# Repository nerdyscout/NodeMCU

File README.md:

# NodeMCU

collection of various PCBs fitting the NodeMCU_ESP8266

## [PIS](PIS) 
- Plant Irrigation System

## [IR](IR) 
- IR-MQTT-Bridge

## [PWR](PWR) 
230V AC phase dimmer

## [CO2](CO2) 
CO2 Measurment with ESP8266
- data can be send via LoRa

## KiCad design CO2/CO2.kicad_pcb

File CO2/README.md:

# NodeMCU_CO2

Shield for the NodeMCU_ESP8266 for builing a CO2 measurment device.

## Schematic

## Layout

## Documentation 
- Assemble all parts according [BOM](gerbers/CO2_BOM_CO2.csv)

#### Software
tbd

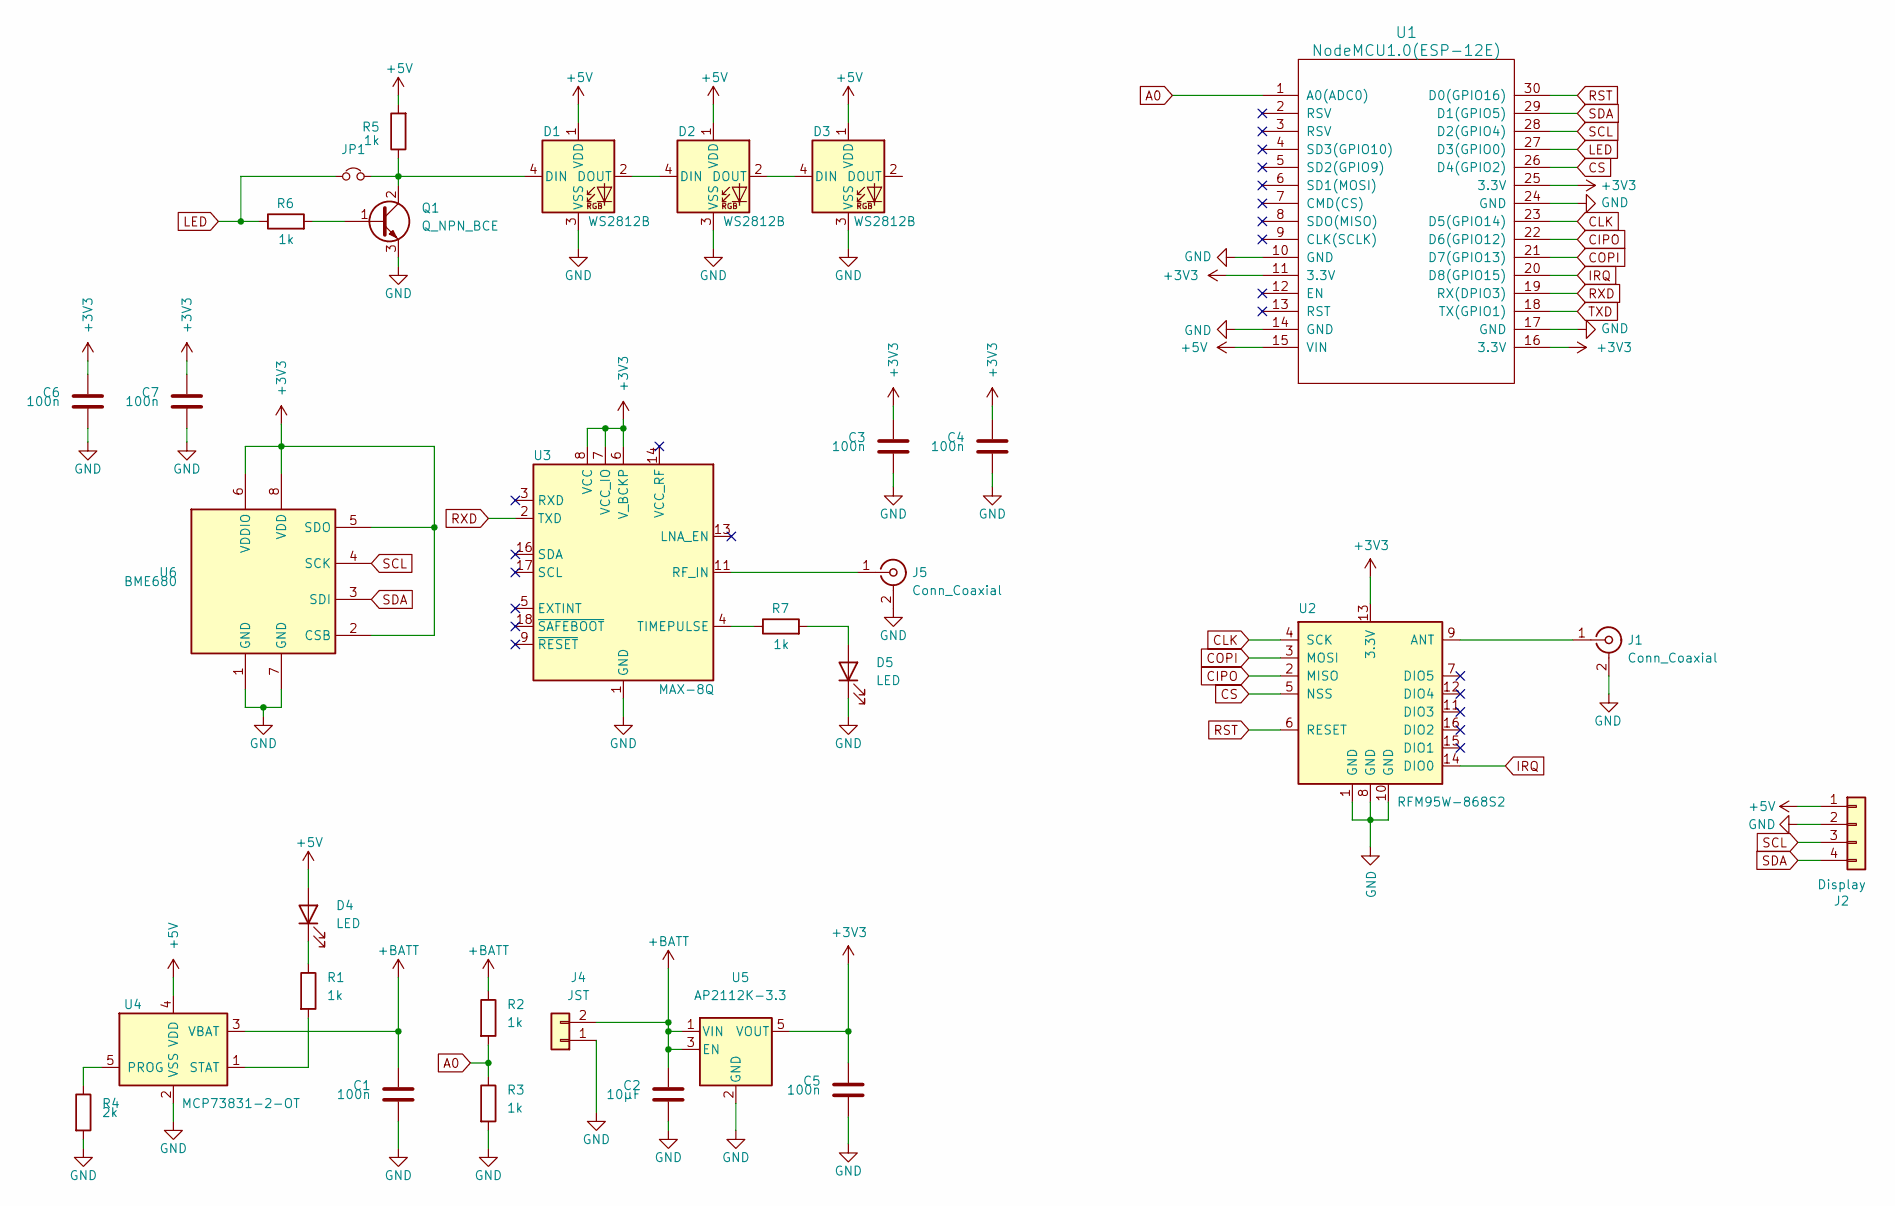
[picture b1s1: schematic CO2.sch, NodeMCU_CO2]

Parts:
C1, C3, C4, C5, C6, C7: 100n; C_0603_1608Metric
C2: 10µF; C_0603_1608Metric
D1, D2, D3: WS2812B; LED_WS2812B_PLCC4_5.0x5.0mm_P3.2mm
D4, D5: LED; LED_0603_1608Metric
J1, J5: Conn_Coaxial; U.FL_Hirose_U.FL-R-SMT-1_Vertical
J2: Display; PinHeader_1x04_P2.54mm_Vertical
J4: JST; JST_PH_S2B-PH-SM4-TB_1x02-1MP_P2.00mm_Horizontal
JP1: Jumper_NC_Small; SolderJumper-2_P1.3mm_Open_RoundedPad1.0x1.5mm
Q1: Q_NPN_BCE; SOT-23
R1, R2, R3, R5, R6, R7: 1k; R_0603_1608Metric
R4: 2k; R_0603_1608Metric
U1: NodeMCU1.0(ESP-12E); NodeMCU_Amica
U2: RFM95W-868S2; HOPERF_RFM9XW_SMD
U3: MAX-8Q; ublox_MAX
U4: MCP73831-2-OT; SOT-23-5
U5: AP2112K-3.3; SOT-23-5
U6: BME680; Bosch_LGA-8_3x3mm_P0.8mm_ClockwisePinNumbering

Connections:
+3V3: C3.2, C4.2, C5.2, C6.2, C7.2, U1.11 (3.3V), U1.16 (3.3V), U1.25 (3.3V), U2.13 (3.3V), U3.6 (V_BCKP), U3.7 (VCC_IO), U3.8 (VCC), U5.5 (VOUT), U6.2 (CSB), U6.5 (SDO), U6.6 (VDDIO), U6.8 (VDD)
+5V: D1.1 (VDD), D2.1 (VDD), D3.1 (VDD), D4.2 (A), J2.1, R5.2, U1.15 (VIN), U4.4 (VDD)
+BATT: C1.2, C2.2, J4.2, R2.1, U4.3 (VBAT), U5.1 (VIN), U5.3 (EN)
A0: R2.2, R3.1, U1.1 (A0(ADC0))
CIPO: U1.22 (D6(GPIO12)), U2.2 (MISO)
CLK: U1.23 (D5(GPIO14)), U2.4 (SCK)
COPI: U1.21 (D7(GPIO13)), U2.3 (MOSI)
CS: U1.26 (D4(GPIO2)), U2.5 (NSS)
GND: C1.1, C2.1, C3.1, C4.1, C5.1, C6.1, C7.1, D1.3 (VSS), D2.3 (VSS), D3.3 (VSS), D5.1 (K), J1.2 (Ext), J2.2, J4.1, J5.2 (Ext), Q1.3 (E), R3.2, R4.2, U1.10 (GND), U1.14 (GND), U1.17 (GND), U1.24 (GND), U2.1 (GND), U2.8 (GND), U2.10 (GND), U3.1 (GND), U3.10 (GND), U3.12 (GND), U4.2 (VSS), U5.2 (GND), U6.1 (GND), U6.7 (GND)
IRQ: U1.20 (D8(GPIO15)), U2.14 (DIO0)
LED: JP1.1, R6.1, U1.27 (D3(GPIO0))
unnamed: D1.2 (DOUT), D2.4 (DIN)
unnamed: D1.4 (DIN), JP1.2, Q1.2 (C), R5.1
unnamed: D2.2 (DOUT), D3.4 (DIN)
unnamed: D4.1 (K), R1.1
unnamed: D5.2 (A), R7.2
unnamed: J1.1 (In), U2.9 (ANT)
unnamed: J5.1 (In), U3.11 (RF_IN)
unnamed: Q1.1 (B), R6.2
unnamed: R1.2, U4.1 (STAT)
unnamed: R4.1, U4.5 (PROG)
unnamed: R7.1, U3.4 (TIMEPULSE)
RST: U1.30 (D0(GPIO16)), U2.6 (RESET)
RXD: U1.19 (RX(DPIO3)), U3.2 (TXD)
SCL: J2.3, U1.28 (D2(GPIO4)), U6.4 (SCK)
SDA: J2.4, U1.29 (D1(GPIO5)), U6.3 (SDI)

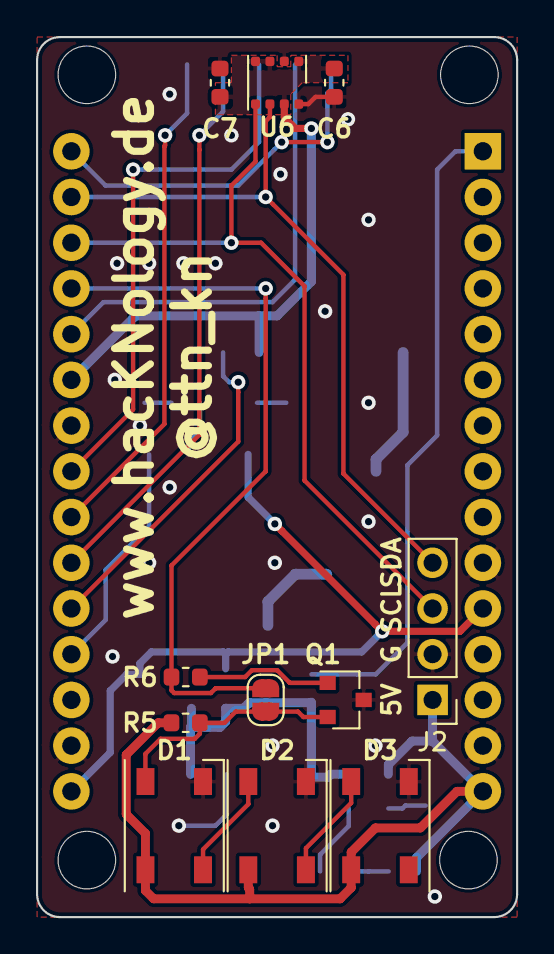
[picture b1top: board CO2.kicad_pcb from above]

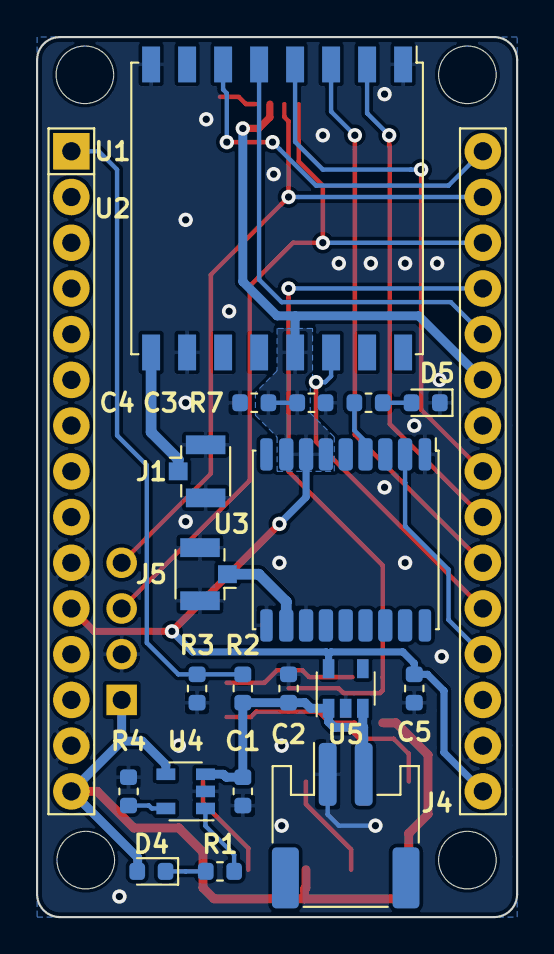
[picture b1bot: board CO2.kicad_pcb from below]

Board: 2 copper layers, 26.7 x 48.9 mm, 31 parts (20 on the bottom side), 26 nets.

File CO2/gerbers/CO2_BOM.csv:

Component;Description;Part;References;Value;Footprint;Quantity Per PCB;Datasheet;variant
1;Unpolarized capacitor;C;C1 C3 C4 C5;100n;C_0603_1608Metric;4;~;
2;Unpolarized capacitor;C;C2;10µF;C_0603_1608Metric;1;~;
3;Light emitting diode;LED;D4 D5;LED;LED_0603_1608Metric;2;~;
4;RGB LED with integrated controller;WS2812B;D1 D2 D3;WS2812B;LED_WS2812B_PLCC4_5.0x5.0mm_P3.2mm;3;https://cdn-shop.adafruit.com/datasheets/WS2812B.pdf;
5;coaxial connector (BNC, SMA, SMB, SMC, Cinch/RCA, ...);Conn_Coaxial;J1 J5;Conn_Coaxial;U.FL_Hirose_U.FL-R-SMT-1_Vertical;2; ~;
6;Generic connector, single row, 01x04, script generated (kicad-library-utils/schlib/autogen/connector/);Conn_01x04;J2;Display;PinHeader_1x04_P2.54mm_Vertical;1;~;PIS
7;Generic connector, single row, 01x02, script generated (kicad-library-utils/schlib/autogen/connector/);Conn_01x02;J4;JST;JST_PH_S2B-PH-SM4-TB_1x02-1MP_P2.00mm_Horizontal;1;~;
8;Generic connector, single row, 01x06, script generated (kicad-library-utils/schlib/autogen/connector/);Conn_01x06;J3;SCD30;PinHeader_1x06_P2.54mm_Vertical;1;~;
9;NPN transistor, base/collector/emitter;Q_NPN_BCE;Q1;Q_NPN_BCE;SOT-23;1;~;
10;Resistor;R;R1 R2 R3 R5 R6 R7;1k;R_0603_1608Metric;6;~;
11;Resistor;R;R4;2k;R_0603_1608Metric;1;~;
12;600mA low dropout linear regulator, with enable pin, 3.8V-6V input voltage range, 3.3V fixed positive output, SOT-23-5 package;AP2112K-3.3;U5;AP2112K-3.3;SOT-23-5;1;https://www.diodes.com/assets/Datasheets/AP2112.pdf;
13;GNSS Module M8, VCC 2.7V to 3.6V;MAX-8Q;U3;MAX-8Q;ublox_MAX;1;https://www.u-blox.com/sites/default/files/MAX-8_DataSheet_%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;
14;Single cell, Li-Ion/Li-Po charge management controller, 4.20V, Tri-State Status Output, in SOT23-5 package;MCP73831-2-OT;U4;MCP73831-2-OT;SOT-23-5;1;http://ww1.microchip.com/downloads/en/DeviceDoc/20001984g.pdf;
15;Low power long range transceiver module, SPI and parallel interface, 868 MHz, spreading factor 6 to12, bandwith 7.8 to 500kHz, -111 to -148 dBm, SMD-16, DIP-16;RFM95W-868S2;U2;RFM95W-868S2;HOPERF_RFM9XW_SMD;1;https://www.hoperf.com/data/upload/portal/20181127/5bfcbea20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;

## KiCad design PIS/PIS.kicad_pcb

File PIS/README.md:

# NodeMCU_PIS

Plant Irrigation Shield for the NodeMCU_ESP8266.

This project combines one soil sensor (resistive or capacetive), one 5V pump in a water tank and a floating switch to detect the water level. Depending on the soil measurment and the configured nominal value the pump can be controlled while the floating switch prevents the pump from running dry. All configurations can be controlled via MQTT.

## Schematic

## Layout

## Assembling

- Assemble all parts according [BOM](gerbers/PIS_BOM_PIS.csv)
  - there are some slight more variants depending if you want to use an capacetive or resestive soil moisture sensor
  - the status LED is optional
  - the pullup/pulldown resistors should only be placed if needed 
  - leave JP1 open

## Software
you could run [Tasmota](https://github.com/arendst/Tasmota) and set a few configurations

and set some extra parameter in console

```
# set nominal value
mem1 750

# turn pump on/off depending mem value
Rule1 on analog#a0>%mem1% do power1 1 endon on analog#a0<%mem1% do power1 0 endon 

# turn rule1 off when water empty // todo: turn status LED on
Rule2 on Power2#State=0 do Rule1 1 endon on Power2#State=1 do Backlog Rule1 0; Power1 0 endon

Rule1 on
Rule2 on
```

Changing mem1 value (can also be done via MQTT) results in new nominal value, every plant may need other value depending on size, soil, sunlight, ... so you need to play a bit to find a good value.

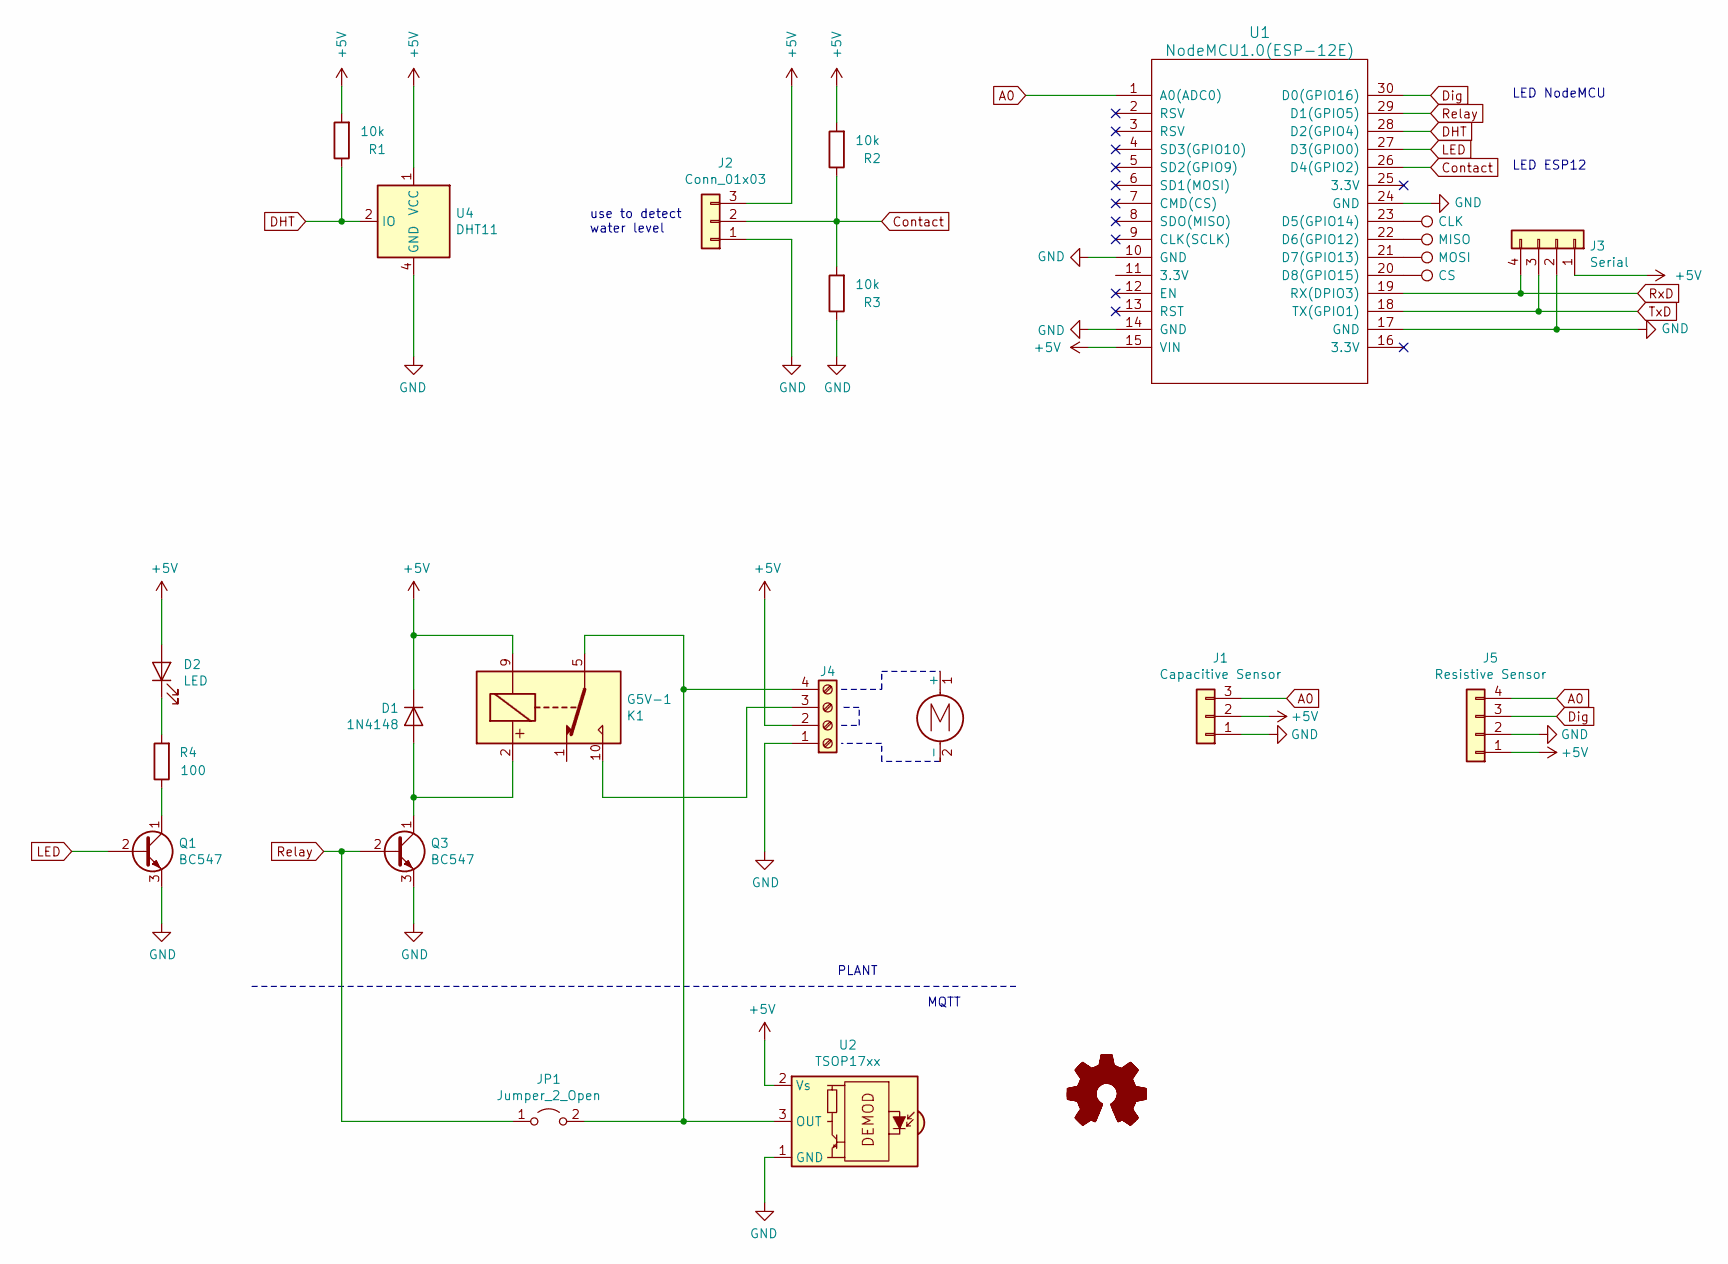
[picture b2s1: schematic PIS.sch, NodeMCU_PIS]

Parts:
D1: 1N4148; D_DO-35_SOD27_P7.62mm_Horizontal
D2: LED; LED_D5.0mm
J1: Capacitive Sensor; PinHeader_1x03_P2.54mm_Vertical
J2: Conn_01x03; PinHeader_1x03_P2.54mm_Vertical
J3: Serial; PinHeader_1x04_P2.54mm_Vertical
J4: Screw_Terminal_01x04; TerminalBlock_TE_282834-4_1x04_P2.54mm_Horizontal
J5: Resistive Sensor; PinHeader_1x04_P2.54mm_Vertical
JP1: Jumper_2_Open; SolderJumper-2_P1.3mm_Open_Pad1.0x1.5mm
K1: G5V-1; Relay_SPDT_Omron_G5V-1
LOGO1: Logo_Open_Hardware_Small; OSHW-Symbol_6.7x6mm_SilkScreen
LOGO2: Logo_Open_Hardware_Small; KiCad-Logo_6mm_SilkScreen
Q1, Q3: BC547; TO-92_Inline; Part Number BC547-ND
R1, R2, R3: 10k; R_Axial_DIN0204_L3.6mm_D1.6mm_P7.62mm_Horizontal
R4: 100; R_Axial_DIN0204_L3.6mm_D1.6mm_P7.62mm_Horizontal
TP1: CLK; TestPoint_Pad_D1.5mm
TP2: MISO; TestPoint_Pad_D1.5mm
TP3: MOSI; TestPoint_Pad_D1.5mm
TP4: CS; TestPoint_Pad_D1.5mm
U1: NodeMCU1.0(ESP-12E); NodeMCU_Amica
U2: TSOP17xx; Vishay_CAST-3Pin
U4: DHT11; PinSocket_1x04_P2.54mm_Vertical; Part Number 1528-1228-ND

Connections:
+5V: D1.1 (K), D2.2 (A), J1.2, J2.3, J3.1, J4.2, J5.1, K1.9, R1.2, R2.2, U1.15 (VIN), U2.2 (Vs), U4.1 (VCC)
A0: J1.3, J5.4, U1.1 (A0(ADC0))
Contact: J2.2, R2.1, R3.2, U1.26 (D4(GPIO2))
DHT: R1.1, U1.28 (D2(GPIO4)), U4.2 (IO)
Dig: J5.3, U1.30 (D0(GPIO16))
GND: J1.1, J2.1, J3.2, J4.1, J5.2, Q1.3 (E), Q3.3 (E), R3.1, U1.10 (GND), U1.14 (GND), U1.17 (GND), U1.24 (GND), U2.1 (GND), U4.4 (GND)
LED: Q1.2 (B), U1.27 (D3(GPIO0))
unnamed: D1.2 (A), K1.2, Q3.1 (C)
unnamed: D2.1 (K), R4.2
unnamed: J4.3, K1.10
unnamed: J4.4, JP1.2 (B), K1.5, K1.6, U2.3 (OUT)
unnamed: Q1.1 (C), R4.1
unnamed: TP1.1, U1.23 (D5(GPIO14))
unnamed: TP2.1, U1.22 (D6(GPIO12))
unnamed: TP3.1, U1.21 (D7(GPIO13))
unnamed: TP4.1, U1.20 (D8(GPIO15))
Relay: JP1.1 (A), Q3.2 (B), U1.29 (D1(GPIO5))
RxD: J3.4, U1.19 (RX(DPIO3))
TxD: J3.3, U1.18 (TX(GPIO1))

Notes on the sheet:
LED NodeMCU
LED ESP12
PLANT
MQTT
use to detect water level

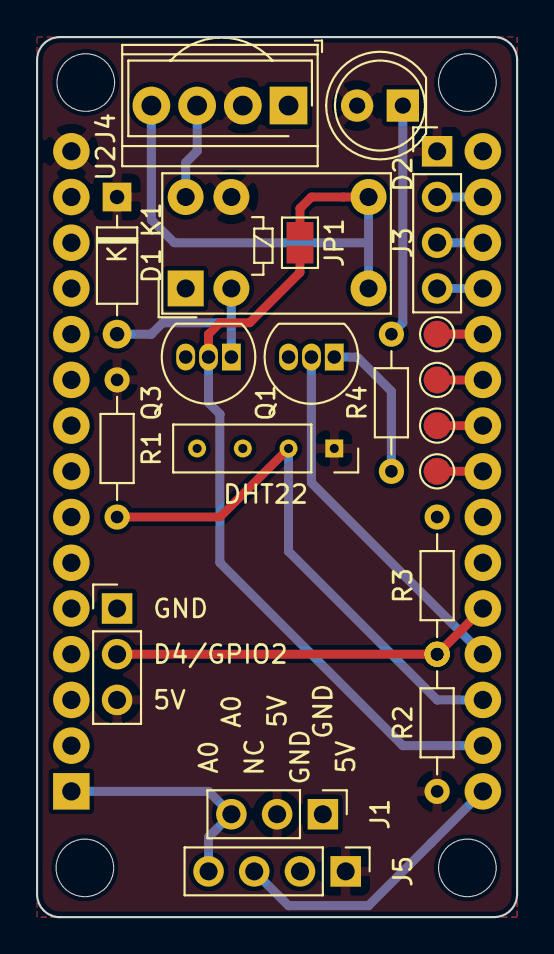
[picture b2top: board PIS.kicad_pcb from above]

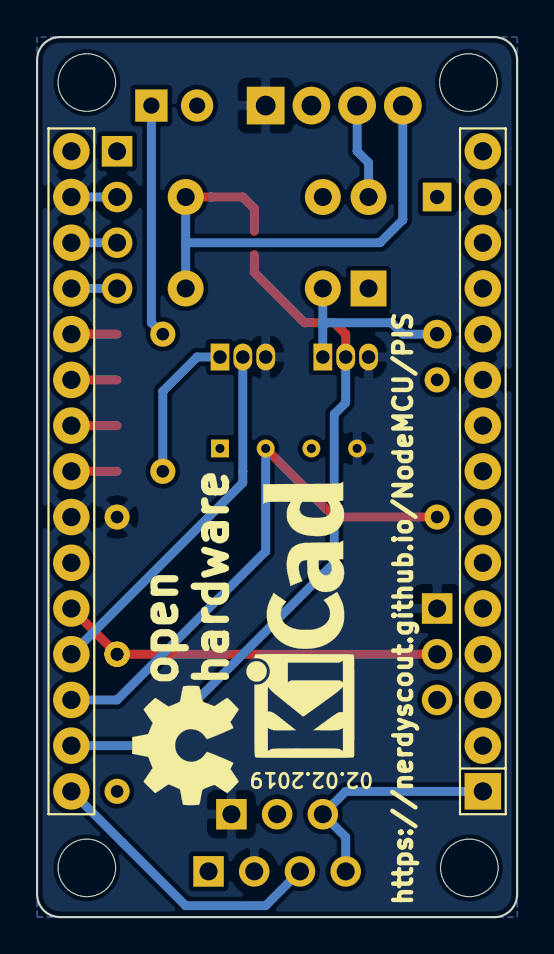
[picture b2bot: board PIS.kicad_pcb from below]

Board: 2 copper layers, 26.7 x 48.9 mm, 24 parts (3 on the bottom side), 19 nets.

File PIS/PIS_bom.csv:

Reference, Quantity,Value,Footprint,Datasheet,Variant,Distributor,Part Number
D1 ,1,1N4148,Diode_THT:D_DO-35_SOD27_P7.62mm_Horizontal,http://www.nxp.com/documents/data_sheet/1N4148_1N4448.pdf,PLANT,,
D2 ,1,LED,LED_THT:LED_D5.0mm,~,"PLANT, MQTT",,
J1 ,1,Capacitive Sensor,Connector_PinHeader_2.54mm:PinHeader_1x03_P2.54mm_Vertical,~,PLANT,,
J2 ,1,Conn_01x03,Connector_PinHeader_2.54mm:PinHeader_1x03_P2.54mm_Vertical,~,PLANT,,
J4 ,1,Screw_Terminal_01x04,TerminalBlock_TE-Connectivity:TerminalBlock_TE_282834-4_1x04_P2.54mm_Horizontal,~,PLANT,,
J5 ,1,Resistive Sensor,Connector_PinHeader_2.54mm:PinHeader_1x04_P2.54mm_Vertical,~,PLANT,,
K1 ,1,G5V-1,Relay_THT:Relay_SPDT_Omron_G5V-1,http://omronfs.omron.com/en_US/ecb/products/pdf/en-g5v_1.pdf,PLANT,,
Q3 Q1 ,2,BC547,Package_TO_SOT_THT:TO-92_Inline,http://www.fairchildsemi.com/ds/BC/BC547.pdf,PLANT,DigiKey,BC547-ND
R1 R2 R3 ,3,10k,Resistor_THT:R_Axial_DIN0204_L3.6mm_D1.6mm_P7.62mm_Horizontal,~,PLANT,,
R4 ,1,100,Resistor_THT:R_Axial_DIN0204_L3.6mm_D1.6mm_P7.62mm_Horizontal,~,"PLANT, MQTT",,
U1 ,1,NodeMCU1.0(ESP-12E),Module:NodeMCU_Amica,,"PLANT, MQTT",,
U2 ,1,TSOP17xx,OptoDevice:Vishay_CAST-3Pin,http://www.micropik.com/PDF/tsop17xx.pdf,MQTT,,
U4 ,1,DHT11,Connector_PinSocket_2.54mm:PinSocket_1x04_P2.54mm_Vertical,http://akizukidenshi.com/download/ds/aosong/DHT11.pdf,PLANT,DigiKey,1528-1228-ND

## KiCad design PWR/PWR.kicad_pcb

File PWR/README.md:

# NodeMCU_Amica_PWR

**Caution** PCB has never been put to production, never tested!

Shield for the NodeMCU_ESP8266 for phase cutting 230V AC :warning:

## Schematic

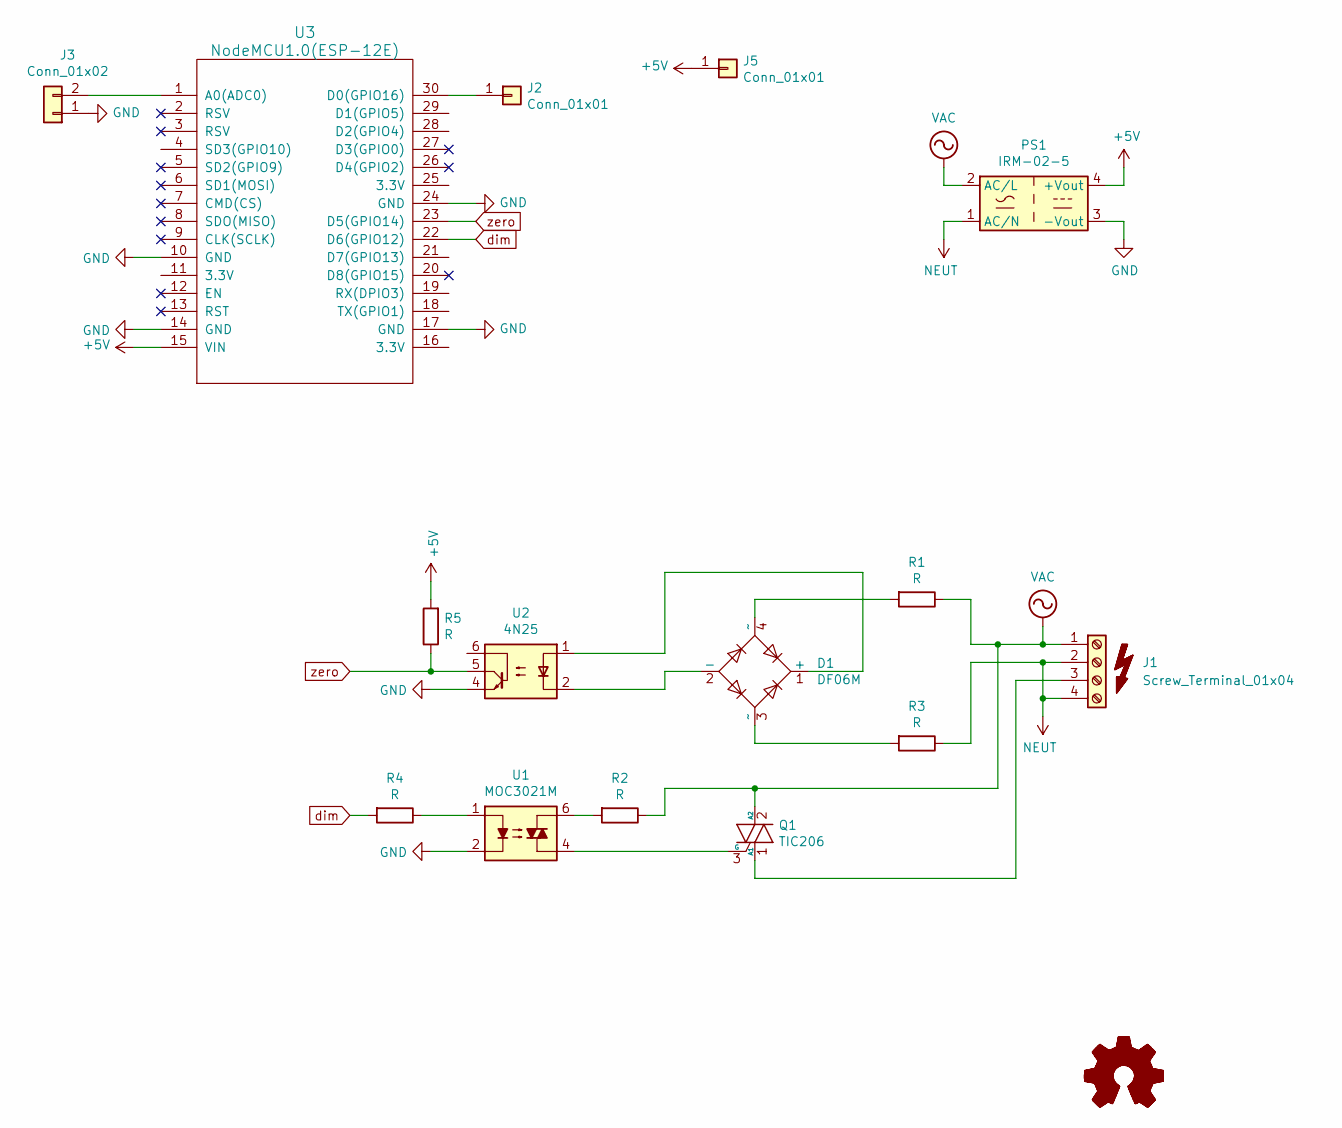
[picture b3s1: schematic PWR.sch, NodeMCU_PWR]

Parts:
D1: DF06M; Diode_Bridge_DIP-4_W7.62mm_P5.08mm; Part Number DF06M-ND
J1: Screw_Terminal_01x04; TerminalBlock_Phoenix_MKDS-1,5-4-5.08_1x04_P5.08mm_Horizont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
J2, J5: Conn_01x01; PinHeader_1x01_P2.54mm_Vertical
J3: Conn_01x02; PinSocket_1x02_P2.54mm_Vertical
LOGO1: Logo_Open_Hardware_Small; OSHW-Symbol_6.7x6mm_SilkScreen
LOGO2: Logo_Open_Hardware_Small; KiCad-Logo_6mm_SilkScreen
PS1: IRM-02-5; Converter_ACDC_MeanWell_IRM-02-xx_THT; Part Number 1866-3009-ND
Q1: TIC206; TO-220-3_Vertical; Part Number 186333 - 62
R1, R2, R3, R4, R5: R; R_Axial_DIN0207_L6.3mm_D2.5mm_P10.16mm_Horizontal
SYM1, SYM2: SYM_Flash_Small; Symbol_Highvoltage_Type1_CopperTop_Small
U1: MOC3021M; DIP-6_W7.62mm; Part Number MOC3021MLT-ND
U2: 4N25; DIP-6_W7.62mm; Part Number 160-1300-5-ND
U3: NodeMCU1.0(ESP-12E); NodeMCU_Amica_WithMountingHoles

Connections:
+5V: J5.1, PS1.4 (+Vout), R5.2, U3.15 (VIN)
GND: J3.1, PS1.3 (-Vout), U1.2, U2.4, U3.10 (GND), U3.14 (GND), U3.17 (GND), U3.24 (GND)
NEUT: J1.2, J1.4, PS1.1 (AC/N), R3.1
unnamed: D1.1 (+), U2.1
unnamed: D1.2 (-), U2.2
unnamed: D1.3 (~~), R3.2
unnamed: D1.4 (~~), R1.2
unnamed: J1.3, Q1.1 (A1)
unnamed: J2.1, U3.30 (D0(GPIO16))
unnamed: J3.2, U3.1 (A0(ADC0))
unnamed: Q1.3 (G), U1.4
unnamed: R2.2, U1.6
unnamed: R4.1, U1.1
VAC: J1.1, PS1.2 (AC/L), Q1.2 (A2), R1.1, R2.1
dim: R4.2, U3.22 (D6(GPIO12))
zero: R5.1, U2.5, U3.23 (D5(GPIO14))

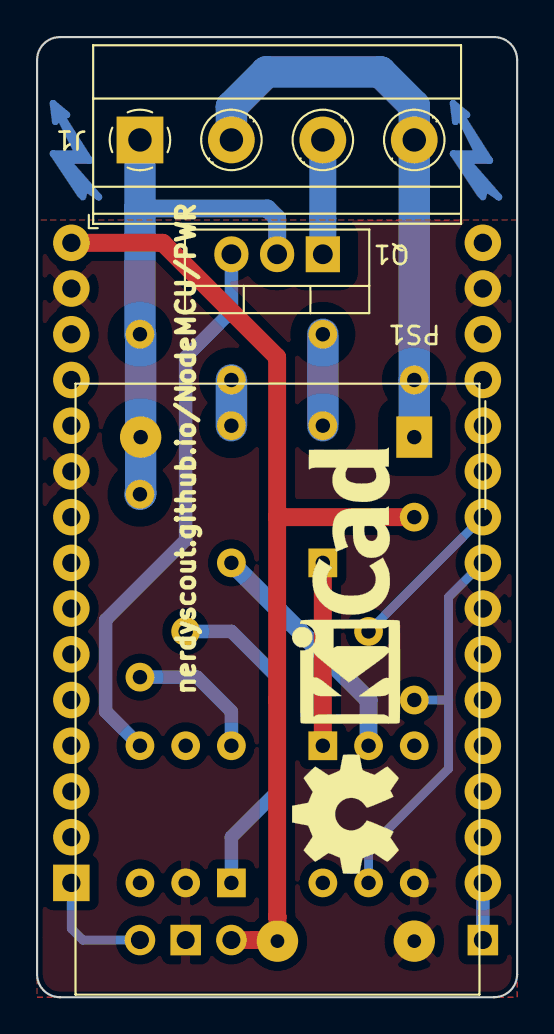
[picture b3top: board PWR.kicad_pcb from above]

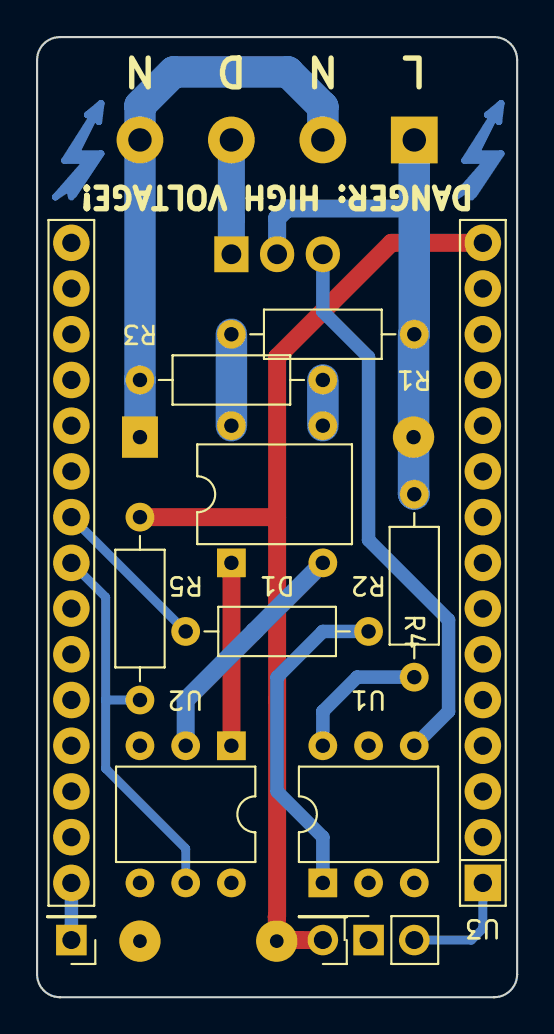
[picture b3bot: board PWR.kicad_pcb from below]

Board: 2 copper layers, 26.7 x 53.3 mm, 19 parts (14 on the bottom side), 16 nets.

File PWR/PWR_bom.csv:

Reference, Value, Footprint, Datasheet, variant, Distributor, Part Number
J1,Screw_Terminal_01x04,"TerminalBlock_Phoenix:TerminalBlock_Phoenix_MKDS-1,5-4-5.08_1x04_P5.08mm_Horizontal",~,"DIM, 5V",,
Q1,TIC206,Package_TO_SOT_THT:TO-220-3_Vertical,http://www.farnell.com/datasheets/56922.pdf,,Conrad,186333 - 62
U1,MOC3021M,Package_DIP:DIP-6_W7.62mm,http://www.fairchildsemi.com/ds/MO/MOC3020M.pdf,DIM,DigiKey,MOC3021MLT-ND
U2,4N25,Package_DIP:DIP-6_W7.62mm,https://www.vishay.com/docs/83725/4n25.pdf,DIM,DigiKey,160-1300-5-ND
R1,R,Resistor_THT:R_Axial_DIN0207_L6.3mm_D2.5mm_P10.16mm_Horizontal,~,DIM,,
R3,R,Resistor_THT:R_Axial_DIN0207_L6.3mm_D2.5mm_P10.16mm_Horizontal,~,DIM,,
D1,DF06M,Diode_THT:Diode_Bridge_DIP-4_W7.62mm_P5.08mm,http://www.vishay.com/docs/88571/dfm.pdf,DIM,DigiKey,DF06M-ND
R2,R,Resistor_THT:R_Axial_DIN0207_L6.3mm_D2.5mm_P10.16mm_Horizontal,~,DIM,,
R4,R,Resistor_THT:R_Axial_DIN0207_L6.3mm_D2.5mm_P10.16mm_Horizontal,~,DIM,,
R5,R,Resistor_THT:R_Axial_DIN0207_L6.3mm_D2.5mm_P10.16mm_Horizontal,~,DIM,,
PS1,IRM-02-5,Converter_ACDC:Converter_ACDC_MeanWell_IRM-02-xx_THT,http://www.meanwell.com/productPdf.aspx?i=675,5V,DigiKey,1866-3009-ND
J3,Conn_01x02,Connector_PinSocket_2.54mm:PinSocket_1x02_P2.54mm_Vertical,~,,,
U3,NodeMCU1.0(ESP-12E),Module:NodeMCU_Amica_WithMountingHoles,,DNP,,
J5,Conn_01x01,Connector_PinHeader_2.54mm:PinHeader_1x01_P2.54mm_Vertical,~,,,
J2,Conn_01x01,Connector_PinHeader_2.54mm:PinHeader_1x01_P2.54mm_Vertical,~,,,

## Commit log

2020-03-29 init
2020-03-29 upgrade
2020-03-29 removed project PWR as this never was verified
2020-03-29 PowerfullInfraredSpan
2020-03-29 renamed copper layer
2020-03-29 docu
2020-10-02 first draft
2020-10-03 final board
2020-10-03 add kicad-exports
2020-10-03 fixed DRC error
2020-10-03 update autogenerated files
2020-10-03 Fix PWR_bom.csv path in kitspace.yaml
2020-10-04 kicad-exports and CO2 module
2020-10-04 trigger action
2020-10-04 seperate PIS and IR projects
2020-10-10 add BME680
2020-10-10 prefix NodeMCU to all PCBs and fixed boms
2020-10-22 basic code structure done
2020-10-24 dump
2020-10-28 REFACTOR!
2020-10-28 prepare co2
2020-10-30 do not use this design
